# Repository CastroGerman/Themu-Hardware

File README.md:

# Themu-Hardware
Themu board hardware design.

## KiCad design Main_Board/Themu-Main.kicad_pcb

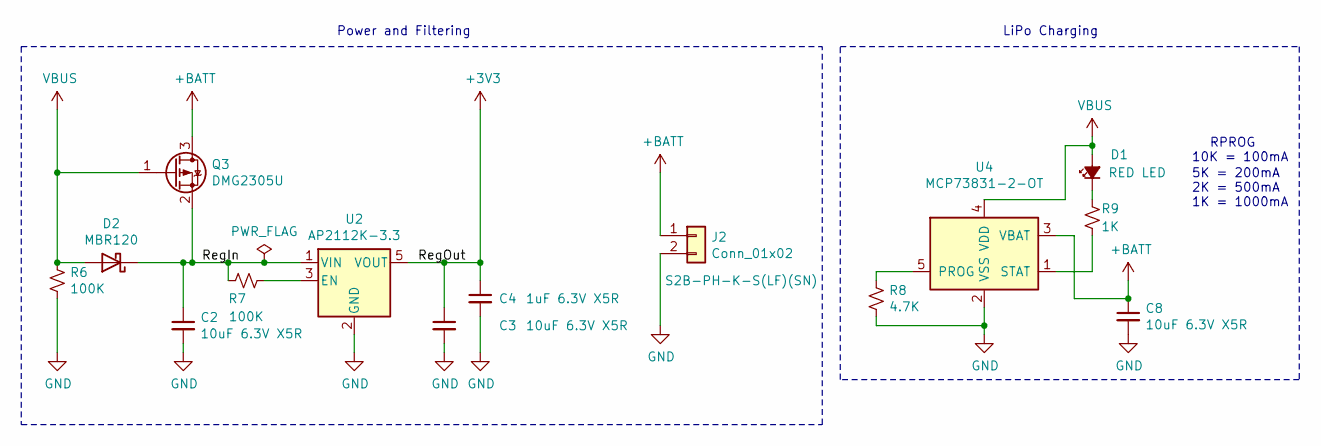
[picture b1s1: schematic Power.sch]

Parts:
C2, C3, C8: 10uF 6.3V X5R; C_0603_1608Metric_Pad1.08x0.95mm_HandSolder
C4: 1uF 6.3V X5R; C_0603_1608Metric_Pad1.05x0.95mm_HandSolder
D1: RED LED; LED_0603_1608Metric_Pad1.05x0.95mm_HandSolder
D2: MBR120; D_SOD-123F
J2: Conn_01x02; JST_PH_S2B-PH-K_1x02_P2.00mm_Horizontal
Q3: DMG2305U; SOT-23
R6, R7: 100K; R_0603_1608Metric_Pad1.05x0.95mm_HandSolder
R8: 4.7K; R_0603_1608Metric_Pad1.05x0.95mm_HandSolder
R9: 1K; R_0603_1608Metric_Pad1.05x0.95mm_HandSolder
U2: AP2112K-3.3; SOT-23-5
U4: MCP73831-2-OT; SOT-23-5

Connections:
+BATT: C8.1, J2.1, Q3.3 (D), U4.3 (VBAT); also elsewhere on the board
/Power/RegIn: C2.1, D2.1 (K), Q3.2 (S), R7.1, U2.1 (VIN)
GND: C2.2, C3.2, C4.2, C8.2, J2.2, R6.2, R8.1, U2.2 (GND), U4.2 (VSS); also elsewhere on the board
unnamed: D1.1 (K), R9.1
unnamed: R7.2, U2.3 (EN)
unnamed: R8.2, U4.5 (PROG)
unnamed: R9.2, U4.1 (STAT)
VBUS: D1.2 (A), D2.2 (A), Q3.1 (G), R6.1, U4.4 (VDD); also elsewhere on the board

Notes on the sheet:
10K = 100mA
5K = 200mA 2K = 500mA 1K = 1000mA
LiPo Charging
Power and Filtering
RPROG

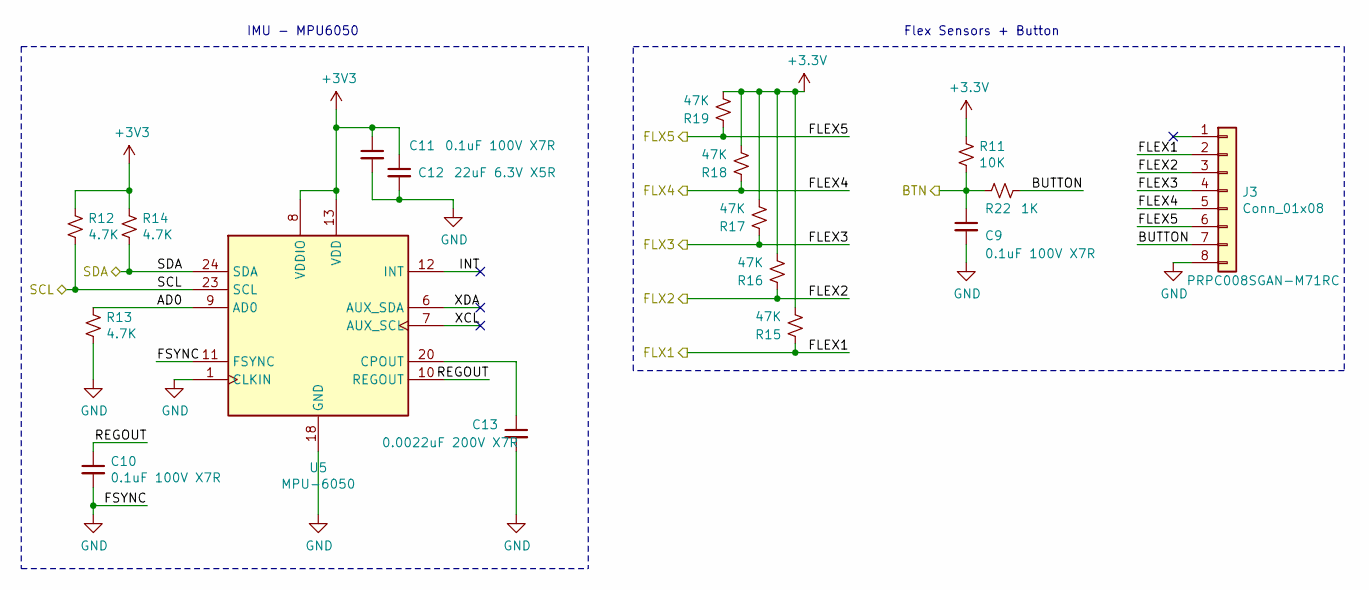
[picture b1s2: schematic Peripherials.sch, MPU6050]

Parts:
C9, C10, C11: 0.1uF 100V X7R; C_0603_1608Metric_Pad1.05x0.95mm_HandSolder
C12: 22uF 6.3V X5R; C_0603_1608Metric_Pad1.05x0.95mm_HandSolder
C13: 0.0022uF 200V X7R; C_0603_1608Metric_Pad1.05x0.95mm_HandSolder
J3: Conn_01x08; PinHeader_1x08_P2.54mm_Horizontal
R11: 10K; R_0603_1608Metric_Pad1.05x0.95mm_HandSolder
R12, R13, R14: 4.7K; R_0603_1608Metric_Pad1.05x0.95mm_HandSolder
R15, R16, R17, R18, R19: 47K; R_0603_1608Metric_Pad1.05x0.95mm_HandSolder
R22: 1K; R_0603_1608Metric_Pad1.05x0.95mm_HandSolder
U5: MPU-6050; InvenSense_QFN-24_4x4mm_P0.5mm

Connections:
/ESP32-WROOM-32/BTN: C9.1, R11.2, R22.2; also elsewhere on the board
/ESP32-WROOM-32/FLX1: J3.2, R15.2; also elsewhere on the board
/ESP32-WROOM-32/FLX2: J3.3, R16.2; also elsewhere on the board
/ESP32-WROOM-32/FLX3: J3.4, R17.2; also elsewhere on the board
/ESP32-WROOM-32/FLX4: J3.5, R18.2; also elsewhere on the board
/ESP32-WROOM-32/FLX5: J3.6, R19.2; also elsewhere on the board
/ESP32-WROOM-32/SCL: R12.2, U5.23 (SCL); also elsewhere on the board
/ESP32-WROOM-32/SDA: R14.2, U5.24 (SDA); also elsewhere on the board
/Peripherials/AD0: R13.1, U5.9 (AD0)
/Peripherials/BUTTON: J3.7, R22.1
/Peripherials/INT: U5.12 (INT)
/Peripherials/REGOUT: C10.1, U5.10 (REGOUT)
/Peripherials/XCL: U5.7 (AUX_SCL)
/Peripherials/XDA: U5.6 (AUX_SDA)
GND: C9.2, C10.2, C11.2, C12.2, C13.2, J3.8, R13.2, U5.1 (CLKIN), U5.11 (FSYNC), U5.18 (GND); also elsewhere on the board
unnamed: C13.1, U5.20 (CPOUT)

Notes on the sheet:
IMU - MPU6050
Flex Sensors + Button

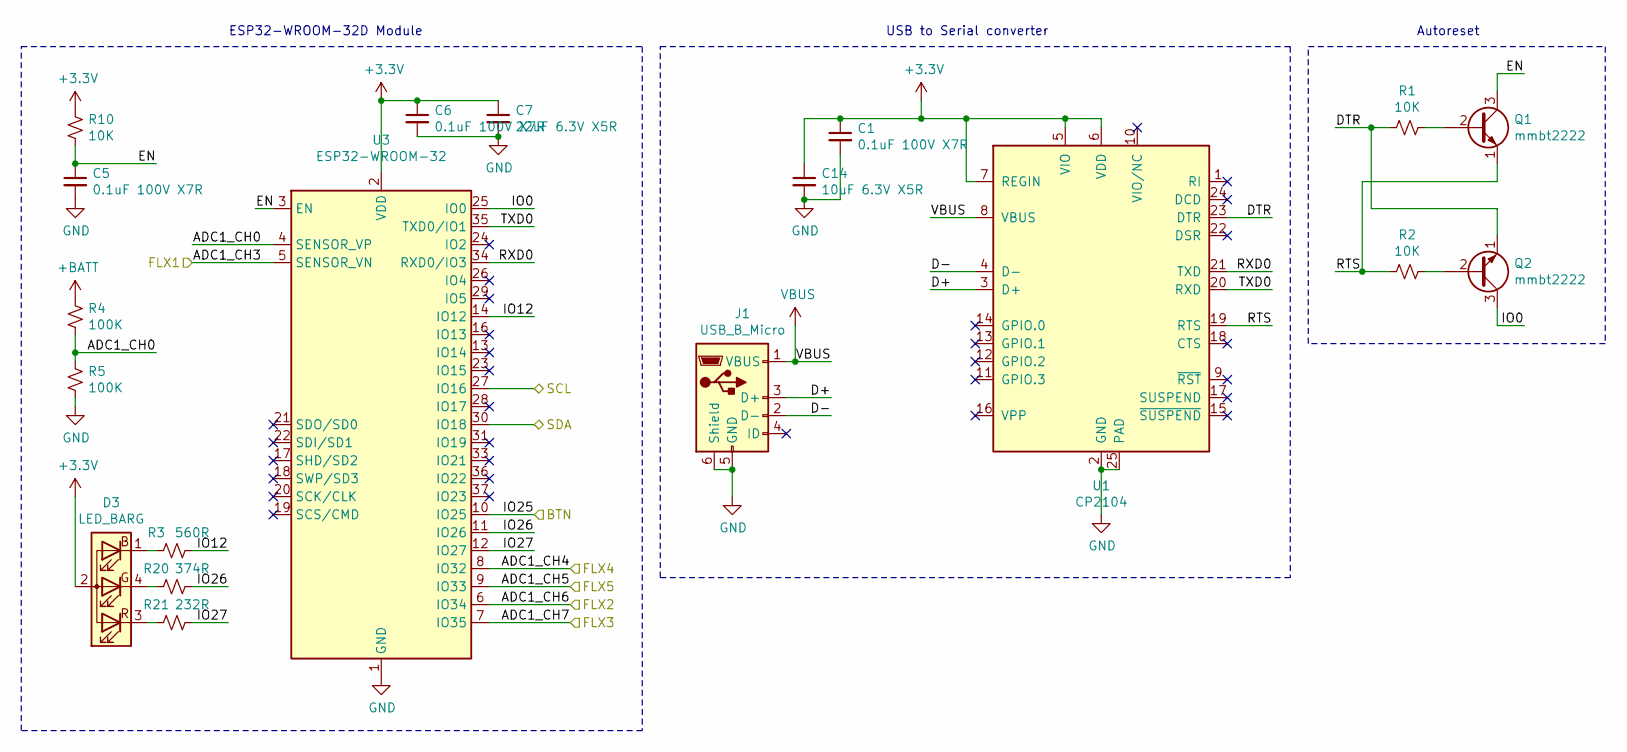
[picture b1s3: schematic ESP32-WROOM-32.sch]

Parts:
C1, C5, C6: 0.1uF 100V X7R; C_0603_1608Metric_Pad1.05x0.95mm_HandSolder
C7: 22uF 6.3V X5R; C_0603_1608Metric_Pad1.05x0.95mm_HandSolder
C14: 10uF 6.3V X5R; C_0603_1608Metric_Pad1.08x0.95mm_HandSolder
D3: LED_BARG; LED-160-80180
J1: USB_B_Micro; USB_Micro-B_Molex-105017-0001
Q1, Q2: mmbt2222; SOT-23
R1, R2, R10: 10K; R_0603_1608Metric_Pad1.05x0.95mm_HandSolder
R3: 560R; R_0603_1608Metric_Pad1.05x0.95mm_HandSolder
R4, R5: 100K; R_0603_1608Metric_Pad1.05x0.95mm_HandSolder
R20: 374R; R_0603_1608Metric_Pad1.05x0.95mm_HandSolder
R21: 232R; R_0603_1608Metric_Pad1.05x0.95mm_HandSolder
U1: CP2104; QFN-24-1EP_4x4mm_P0.5mm_EP2.6x2.6mm
U3: ESP32-WROOM-32

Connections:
+BATT: R4.1; also elsewhere on the board
/ESP32-WROOM-32/ADC1_CH0: R4.2, R5.1, U3.4 (SENSOR_VP)
/ESP32-WROOM-32/BTN: U3.10 (IO25); also elsewhere on the board
/ESP32-WROOM-32/D+: J1.3 (D+), U1.3 (D+)
/ESP32-WROOM-32/D-: J1.2 (D-), U1.4 (D-)
/ESP32-WROOM-32/DTR: Q2.1 (E), R1.2, U1.23 (DTR)
/ESP32-WROOM-32/EN: C5.1, Q1.3 (C), R10.2, U3.3 (EN)
/ESP32-WROOM-32/FLX1: U3.5 (SENSOR_VN); also elsewhere on the board
/ESP32-WROOM-32/FLX2: U3.6 (IO34); also elsewhere on the board
/ESP32-WROOM-32/FLX3: U3.7 (IO35); also elsewhere on the board
/ESP32-WROOM-32/FLX4: U3.8 (IO32); also elsewhere on the board
/ESP32-WROOM-32/FLX5: U3.9 (IO33); also elsewhere on the board
/ESP32-WROOM-32/IO0: Q2.3 (C), U3.25 (IO0)
/ESP32-WROOM-32/IO12: R3.1, U3.14 (IO12)
/ESP32-WROOM-32/IO26: R20.1, U3.11 (IO26)
/ESP32-WROOM-32/IO27: R21.1, U3.12 (IO27)
/ESP32-WROOM-32/RTS: Q1.1 (E), R2.2, U1.19 (RTS)
/ESP32-WROOM-32/RXD0: U1.21 (TXD), U3.34 (RXD0/IO3)
/ESP32-WROOM-32/SCL: U3.27 (IO16); also elsewhere on the board
/ESP32-WROOM-32/SDA: U3.30 (IO18); also elsewhere on the board
/ESP32-WROOM-32/TXD0: U1.20 (RXD), U3.35 (TXD0/IO1)
GND: C1.2, C5.2, C6.2, C7.2, C14.2, J1.5 (GND), J1.6 (Shield), R5.2, U1.2 (GND), U1.25 (PAD), U3.1 (GND), U3.15 (GND), U3.38 (GND), U3.39 (GND); also elsewhere on the board
unnamed: D3.1 (BK), R3.2
unnamed: D3.3 (RK), R21.2
unnamed: D3.4 (GK), R20.2
unnamed: Q1.2 (B), R1.1
unnamed: Q2.2 (B), R2.1
VBUS: J1.1 (VBUS), U1.8 (VBUS); also elsewhere on the board

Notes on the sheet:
USB to Serial converter
Autoreset
ESP32-WROOM-32D Module

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
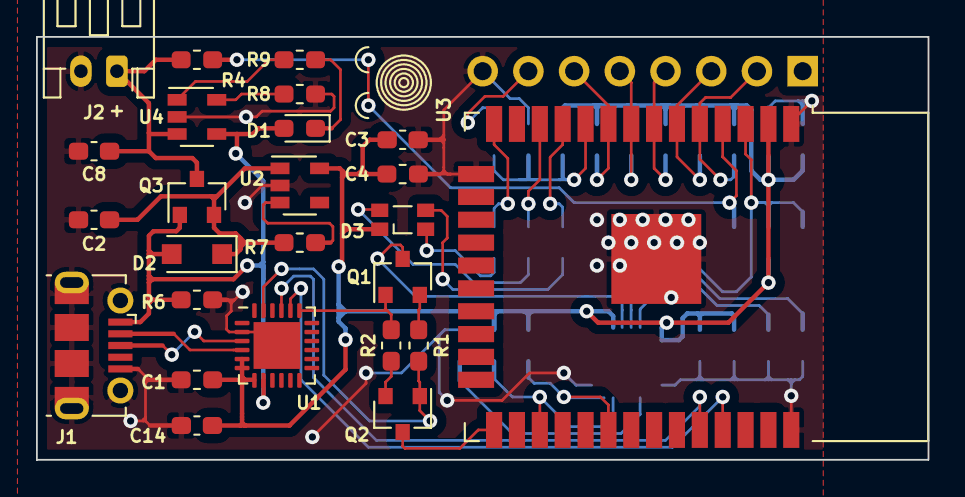
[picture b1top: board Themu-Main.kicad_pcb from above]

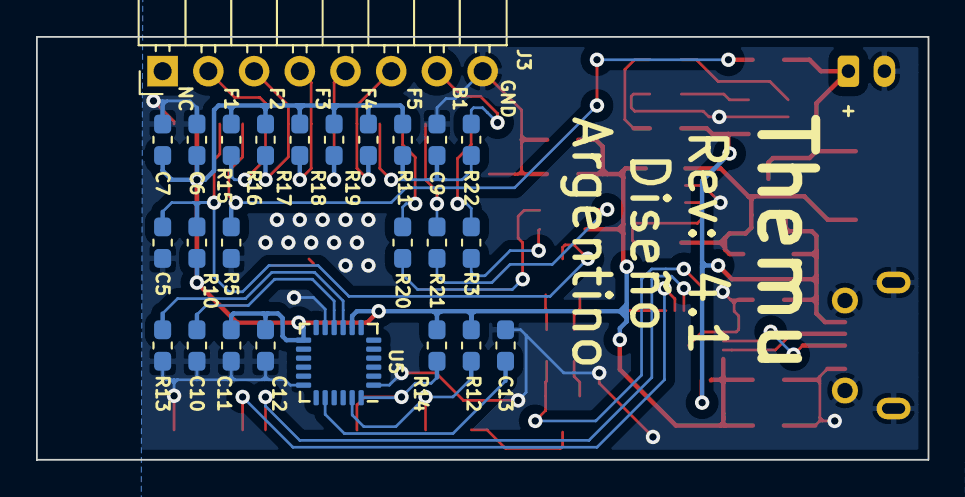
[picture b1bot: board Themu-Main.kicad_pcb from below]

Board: 2 copper layers, 49.5 x 23.5 mm, 50 parts (25 on the bottom side), 38 nets.

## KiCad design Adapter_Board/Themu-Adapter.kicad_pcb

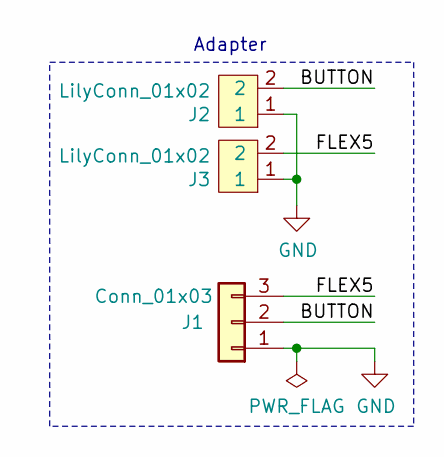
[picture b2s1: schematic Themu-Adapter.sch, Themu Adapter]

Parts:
J1: Conn_01x03; PinSocket_1x03_P2.54mm_Horizontal
J2, J3: LilyConn_01x02; LilyConn_01x02_87mils_130mils

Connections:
/BUTTON: J1.2, J2.2
/FLEX5: J1.3, J3.2
GND: J1.1, J2.1, J3.1

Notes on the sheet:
Adapter

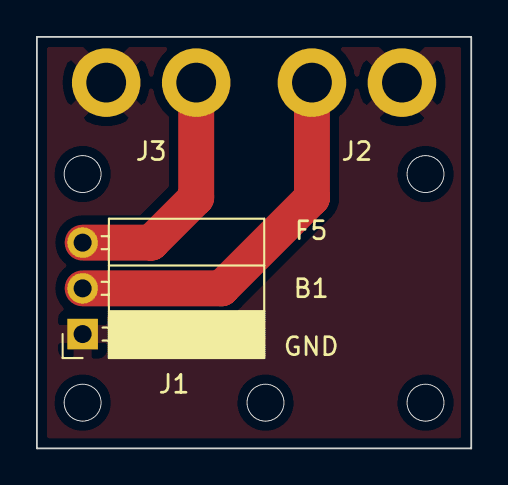
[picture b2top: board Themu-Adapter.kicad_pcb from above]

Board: 2 copper layers, 24.1 x 22.9 mm, 3 parts (0 on the bottom side), 3 nets.

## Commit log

2020-10-06 Initial commit (#1)
2020-10-14 Routed completed
2020-10-15 RGB Led (L1) footprint updated
2020-10-24 Changed tracks routing to fit new design rules. Components placement remain the same.
    New design rules:
    Clearance from 6 mils (0.15 mm) to 8 mils (0.2 mm)
    Via Drill/Size from 12/25 mils (0.3/0.635 mm) to 15.74/31.5 mils (0.4/0.8 mm)
    Thermal spoke width from 8 mils (0.2 mm) to 11.8 mils (0.3 mm)
2020-10-24 Revert "Devel"
2020-10-24 Added adapter board for 5 flex sensors and 1 button
2020-10-31 Partial commit
2020-11-02 Rev 2.0 commit. INTI revision.
2021-01-14 Resolving issues. - Bottom silk legend changed. - New tracing rules added for power supply lines. - D3 led changed for QBLP655R-RGB. 3D model missing.
2021-01-14 Resolving issues. (#9)
    - Bottom silk legend changed.
    - New tracing rules added for power supply lines.
    - D3 led changed for QBLP655R-RGB. 3D model missing.
2021-06-05 Changing I2C pins
2021-06-05 Changing I2C pins (continue)
2021-06-08 New D3 footprint and model
2021-06-08 Generating fabrication outputs
2021-06-12 Fix/i2c (#10)
    * Changing I2C pins
    * Changing I2C pins (continue)
    * New D3 footprint and model
    * Generating fabrication outputs
2021-06-13 C2, C3, C8 and C14 footprints and packages changed from 1210 to 0603
2021-09-17 C2, C3, C8 and C14 footprints and packages changed from 1210 to 0603 (#11)
